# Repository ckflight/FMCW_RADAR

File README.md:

# Frequency Modulated Continuous Wave Radar Hardware Design and the Firmware

Check the new design's Python files for better processing and analysis https://github.com/ckflight/FMCW_RADAR_2v2

#### Later Update 1: 
  New version of the hardware is available in the **Radar 2** folder. For **Radar 2** design, two separated boards in **Radar MCU** and **Radar RF** folders are brought together with several necessary improvements. I recommend using the second design since it is more reliable and tested. The reason behind two separate board was to change digital part of the board without changing the RF part of it. However, one united design performs better and have a better temperature cooling control which affect the overall perfomance significantly.
  
  ##### Important Power Supply Note: I used switching regulator for 3.3 and 5V power sources to test their effect on the RF performance and oscillation of ripple voltage on OpAmp analog amplifier side. Therefore do not use switching regulator in your design. Change them to LDO type of clean supplies. Or add second LDO stage to the switching regulator unless you want an AM modulated ( 1.4 MHz switching freq. is very visible ) signal at the OpAmp side. After observing these affects i had to fine tune components which is not necessary if you use a cleaner source !!!

#### Later Update 2: 
  I have added a new Python script for plotting the radar data with Python Qt5 and Vispy plotting tool which uses GPU instead of CPU. Radar_Plot2.py is the source code. New code plots the time domain and frequency domain data together with scale and restart options. It has thread based approach between Vispy and Qt classes by using DataSource which allows us to manage more data. See first screenshot under Python Script Plots section below.

#### Radar Info:
 * Frequency Modulated Continuous Wave Radar with 26 dBm output power covering around 250 meters range with 10 dBi gain patch antenna (400 meters in theory by using a better ADC with higher sampling rate to match the noise floor of the RF receiver chain).
 
 $$ Range(radar) = {\sqrt[4]{Pt * G^2 * \lambda^2 * \sigma \over Pmin * 4\pi^3}} $$
 
  * Receiver chain has LNA, Gain Block and Mixer. The gain block drops the Noise Figure from 7 dB to 2 dB, which doubles the detection range. To determine the radar detection range, minimum detectable signal is needed. RF receiver chain has thermal noise and it determines the noise floor for Pmin. Signal to Noise (SNR) ratio of 20 dB is assumed for a good detectable signal then:
 
 $$ Pthermal(watt) = {k * T * B * F} $$
 
 $$ Pthermal(dBm) = {10\log_{10} {kT \over 1mW} + NF + 10\log_{10} BW} $$
  
 $$ Pmin(dBm) = {Pthermal(dBm) + 20dB} $$

 * Radar, has an auto gain configuration with a digital potentiometer to control intermediate frequency (IF) signal gain at the last stage of the analog amplifier before sampling with ADC.
 
 * -40 dB / Decade Range Compensation Filter is implemented. Closer objects reflect more powerful RF signal which suppresses the signal of the objects at further distance. By amplifying the weaker signals and filtering the closer ones, each frequency band is adjusted to the same amplitude.
 
 * The IF signal is available at different stages of the amplifier and filter circuit for testing with other configurations.

 * The VCO range of the radar is from 5.5 to 6.1 GHz
 
 * Directional coupler has low insertion loss of 0.25 dB and 16 dB coupling.
 
 * ADF4158 Frequency Synthesizer is available due to the nonlinear characteristics of the VCO profile for accurate distance detection. ADF4158 can generate pulses with some gap between each sweep. During this gap samples are packed and buffered over USB.
 
  * STM32F4's DAC has a triangular waveform generation option and it can be used for VCO signal generation as well. Both option are available on board. Check schematic to populate necessary resistor values to use either mode.
 
 * SMA connector has 1 mm pad size, but the 50 Ohm transmission line is 0.342 mm wide. To prevent reflection, cutout is implemented beneath the SMA pad with CST Studio simulation which is also available at my repository https://github.com/ckflight/CST_ADS_MODELS_SIMULATIONS

 * PCB has 4 layers. 50 Ohm impedance microstrip transmission line is making 0.342mm trace width by using oshpark's stack-up below. Stack-up layer information can be found here: https://docs.oshpark.com/services/four-layer/

 * Main loop runs with a Finite State Machine (FSM) to control radar, which checks the condition of the start of the sweep and the gap. ADF4158 Muxout is generating a pulse according to the sweep condition. External interrupt tracks this pulse to move between FSM states. 

 * Hardware is configured using Python script so the PC is in Host mode and controls everything. In this way, any hardware parameters can be changed without reflashing the firmware.

 * N number of samples are determined by sweep bandwidth rise time and the sampling frequency. 
   For example:

   Fs = 500.000 samples/sec and the sweep rise time is 1 millisecond (ms) for 200 MHz bandwidth. The system will pack 500 x  16 bit ADC samples and transfer 1000 x 8 bit ADC samples to Python script in 1 ms. Therefore, 1 MegaByte data is buffered to Host PC for 500 KHz sampling frequency in 1 second.
  
 * Python Script: I have uploaded an example record file along with python scripts where the peaks of the stationary objects can be seen. 

### Object Type Detection:

 * Object type detection is done with the similar code that i wrote for my project at the repository https://github.com/ckflight/RADAR_24GHZ_NEURAL_NETWORK
 
## RADAR 2 Screenshot:

## RADAR 1 RF Board Screenshot:

## RADAR 1 MCU Board Screenshot:

## Python Script Plots:

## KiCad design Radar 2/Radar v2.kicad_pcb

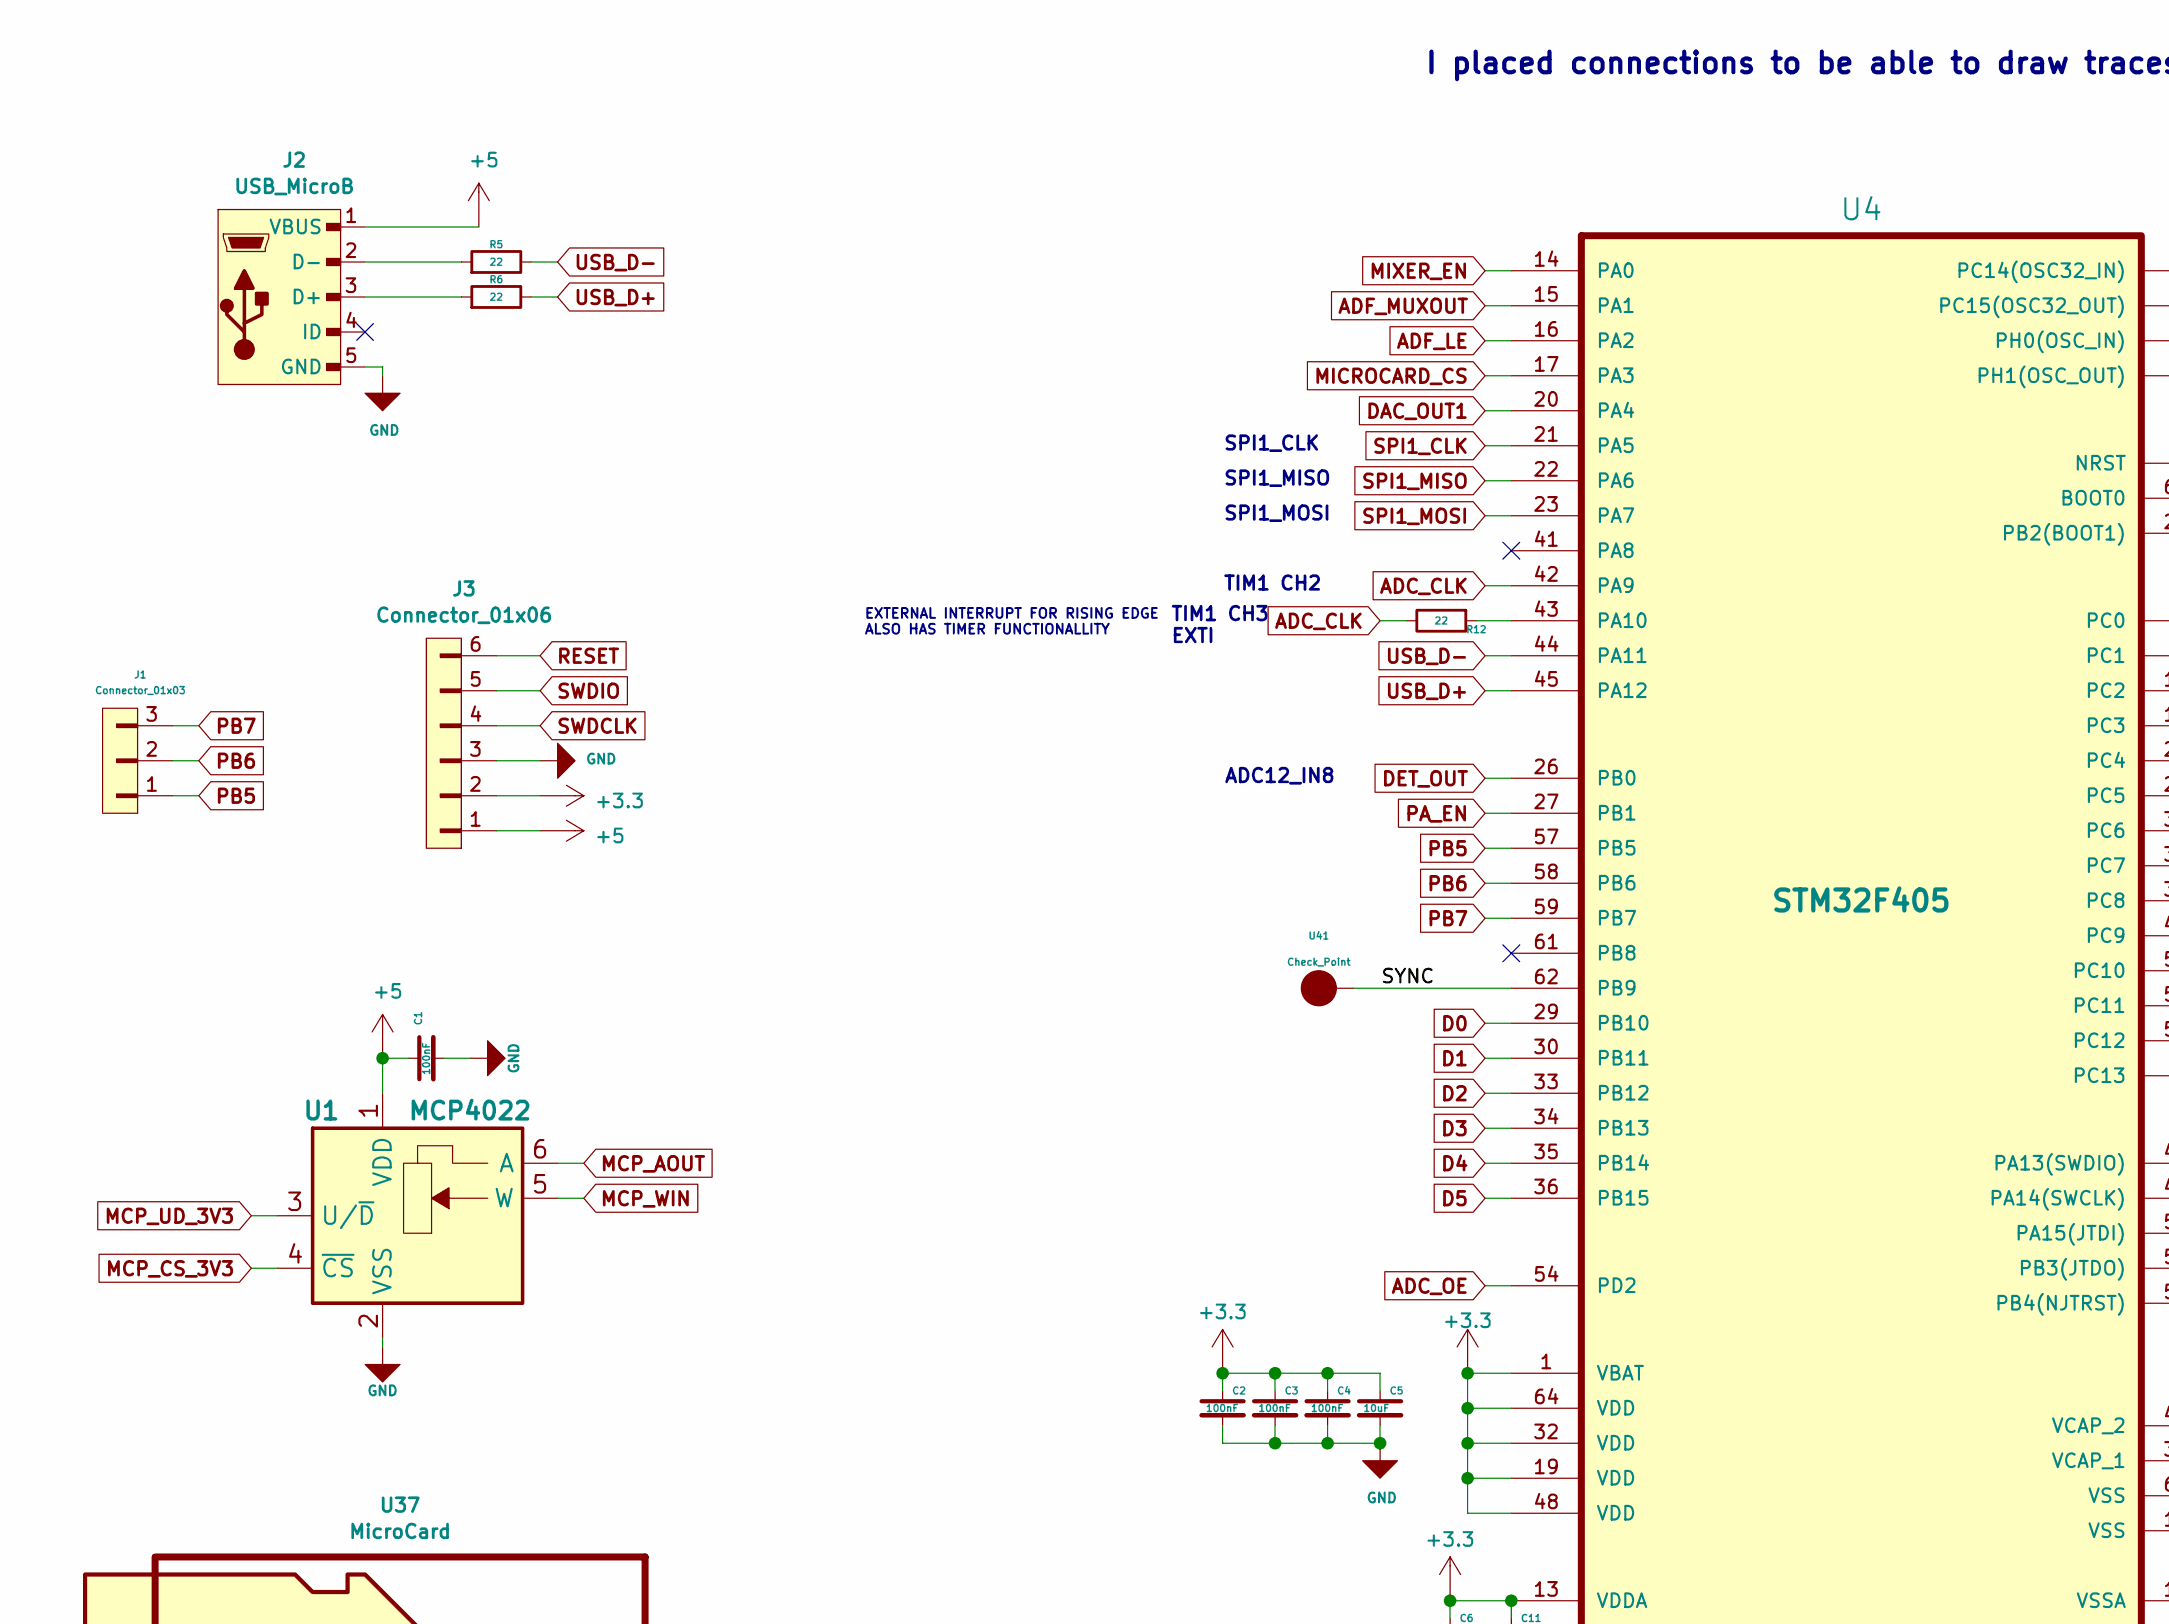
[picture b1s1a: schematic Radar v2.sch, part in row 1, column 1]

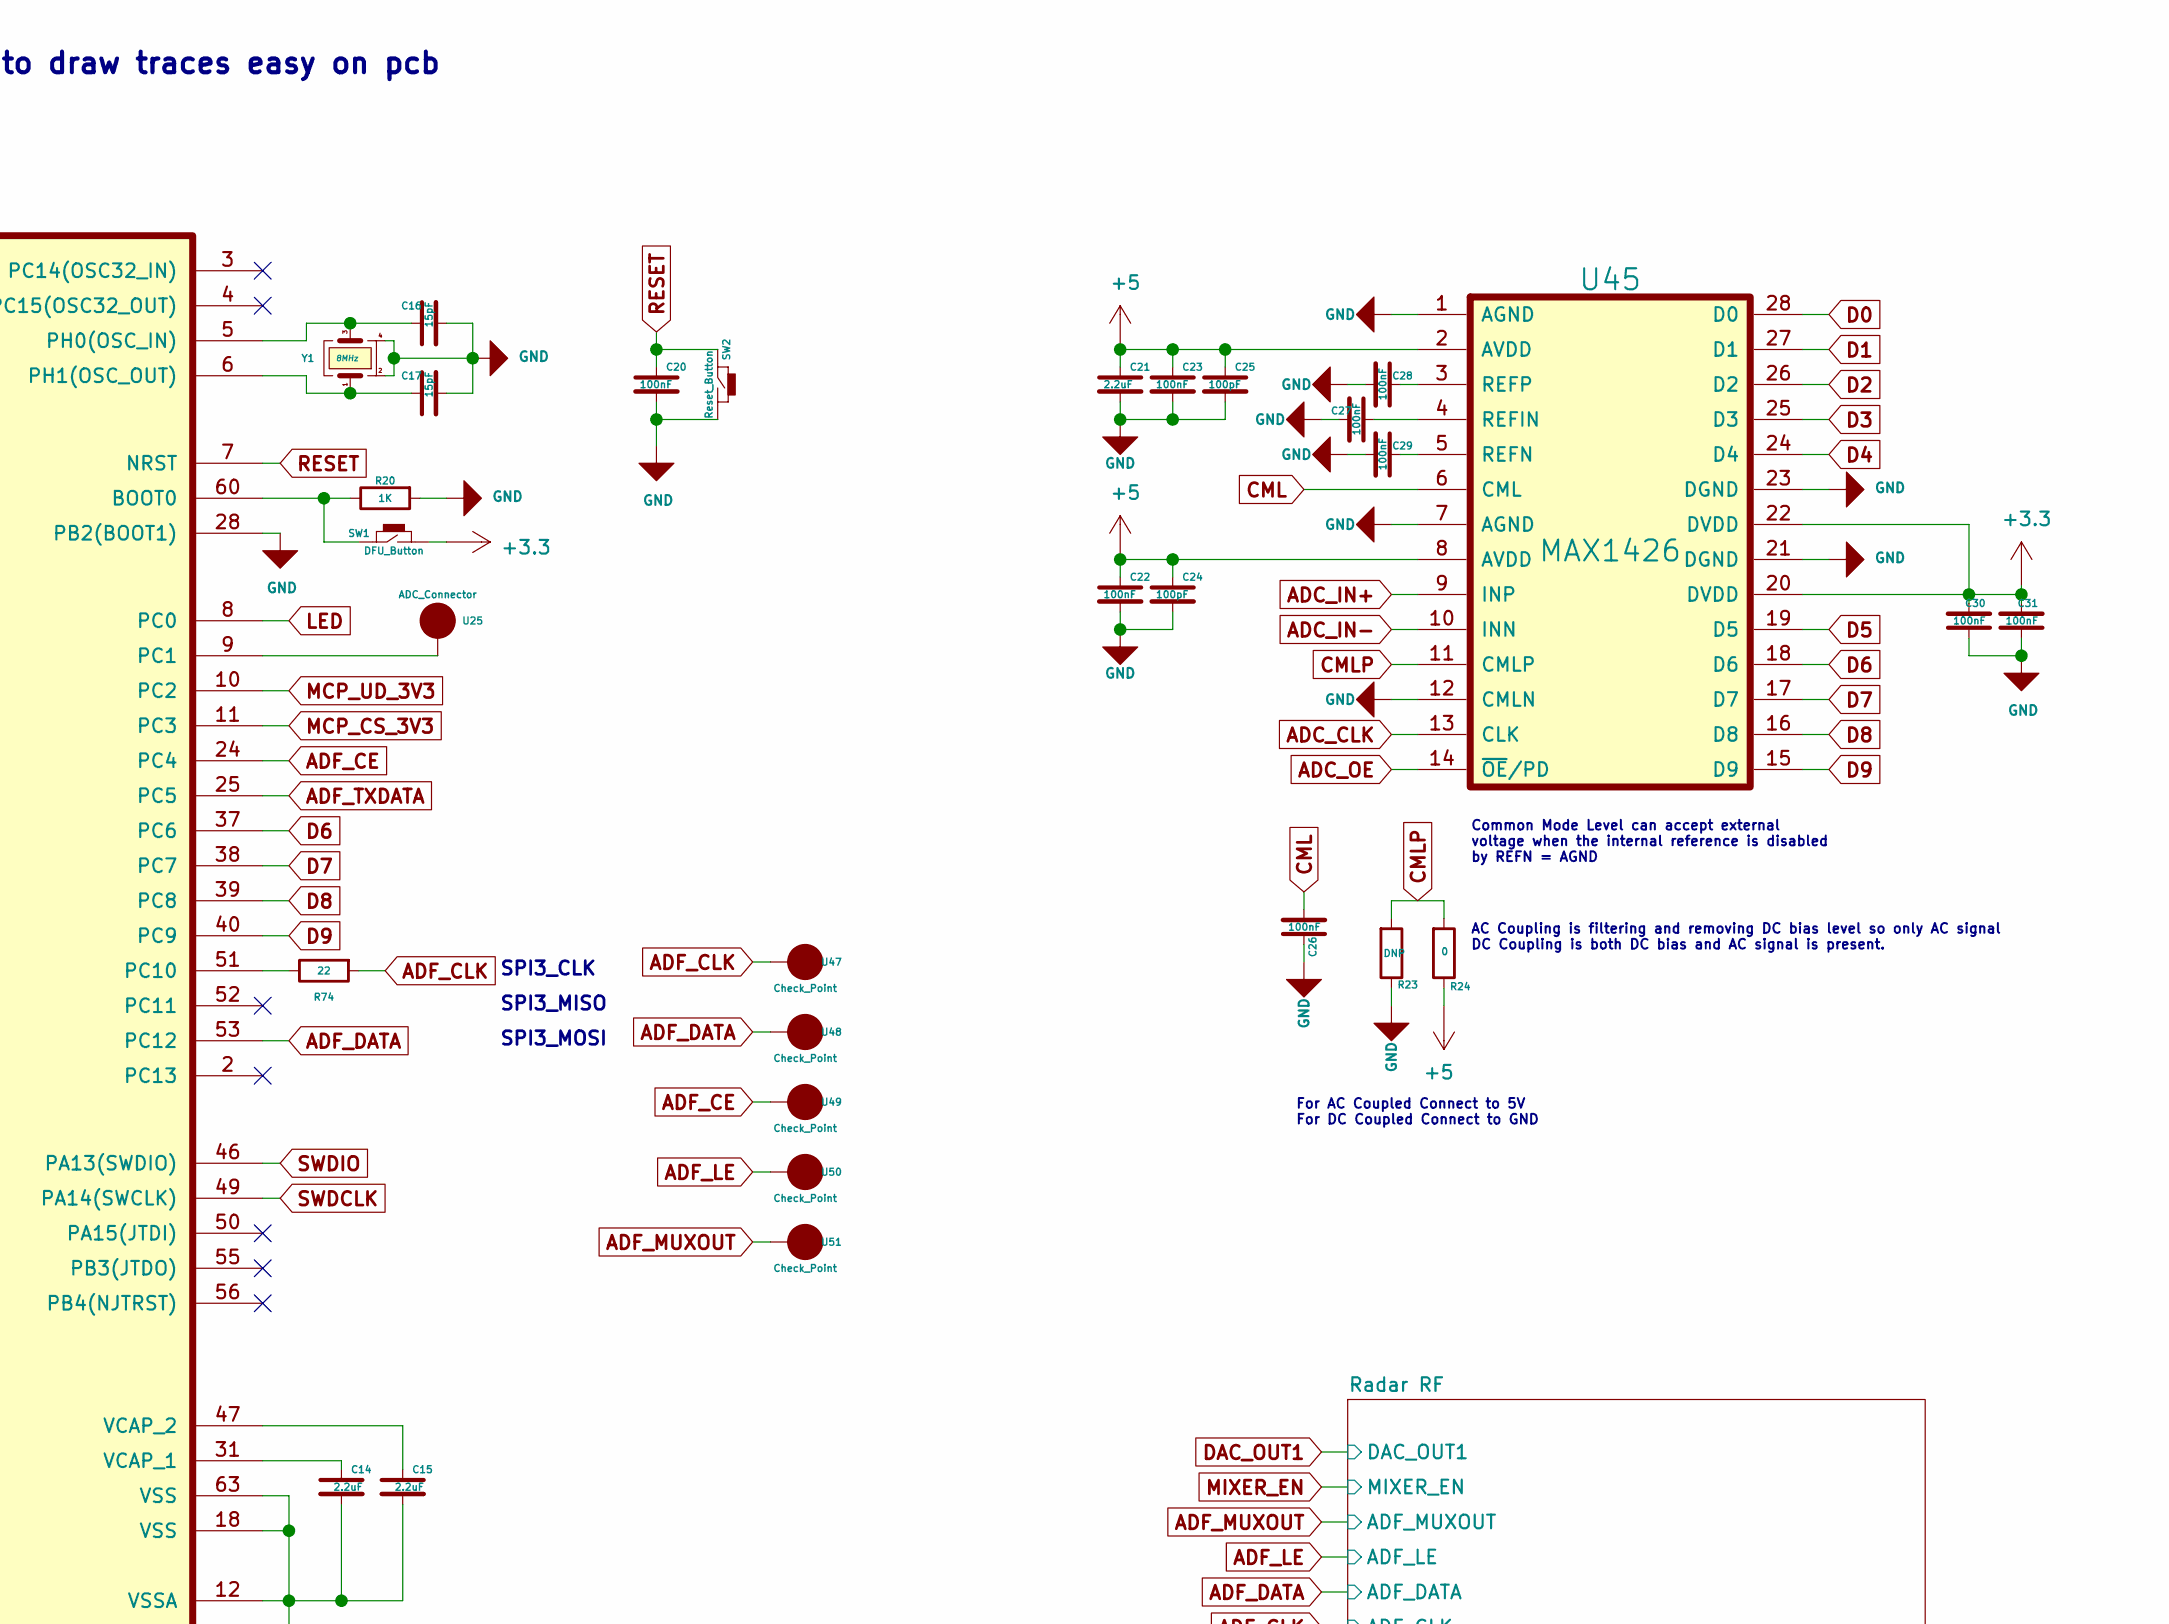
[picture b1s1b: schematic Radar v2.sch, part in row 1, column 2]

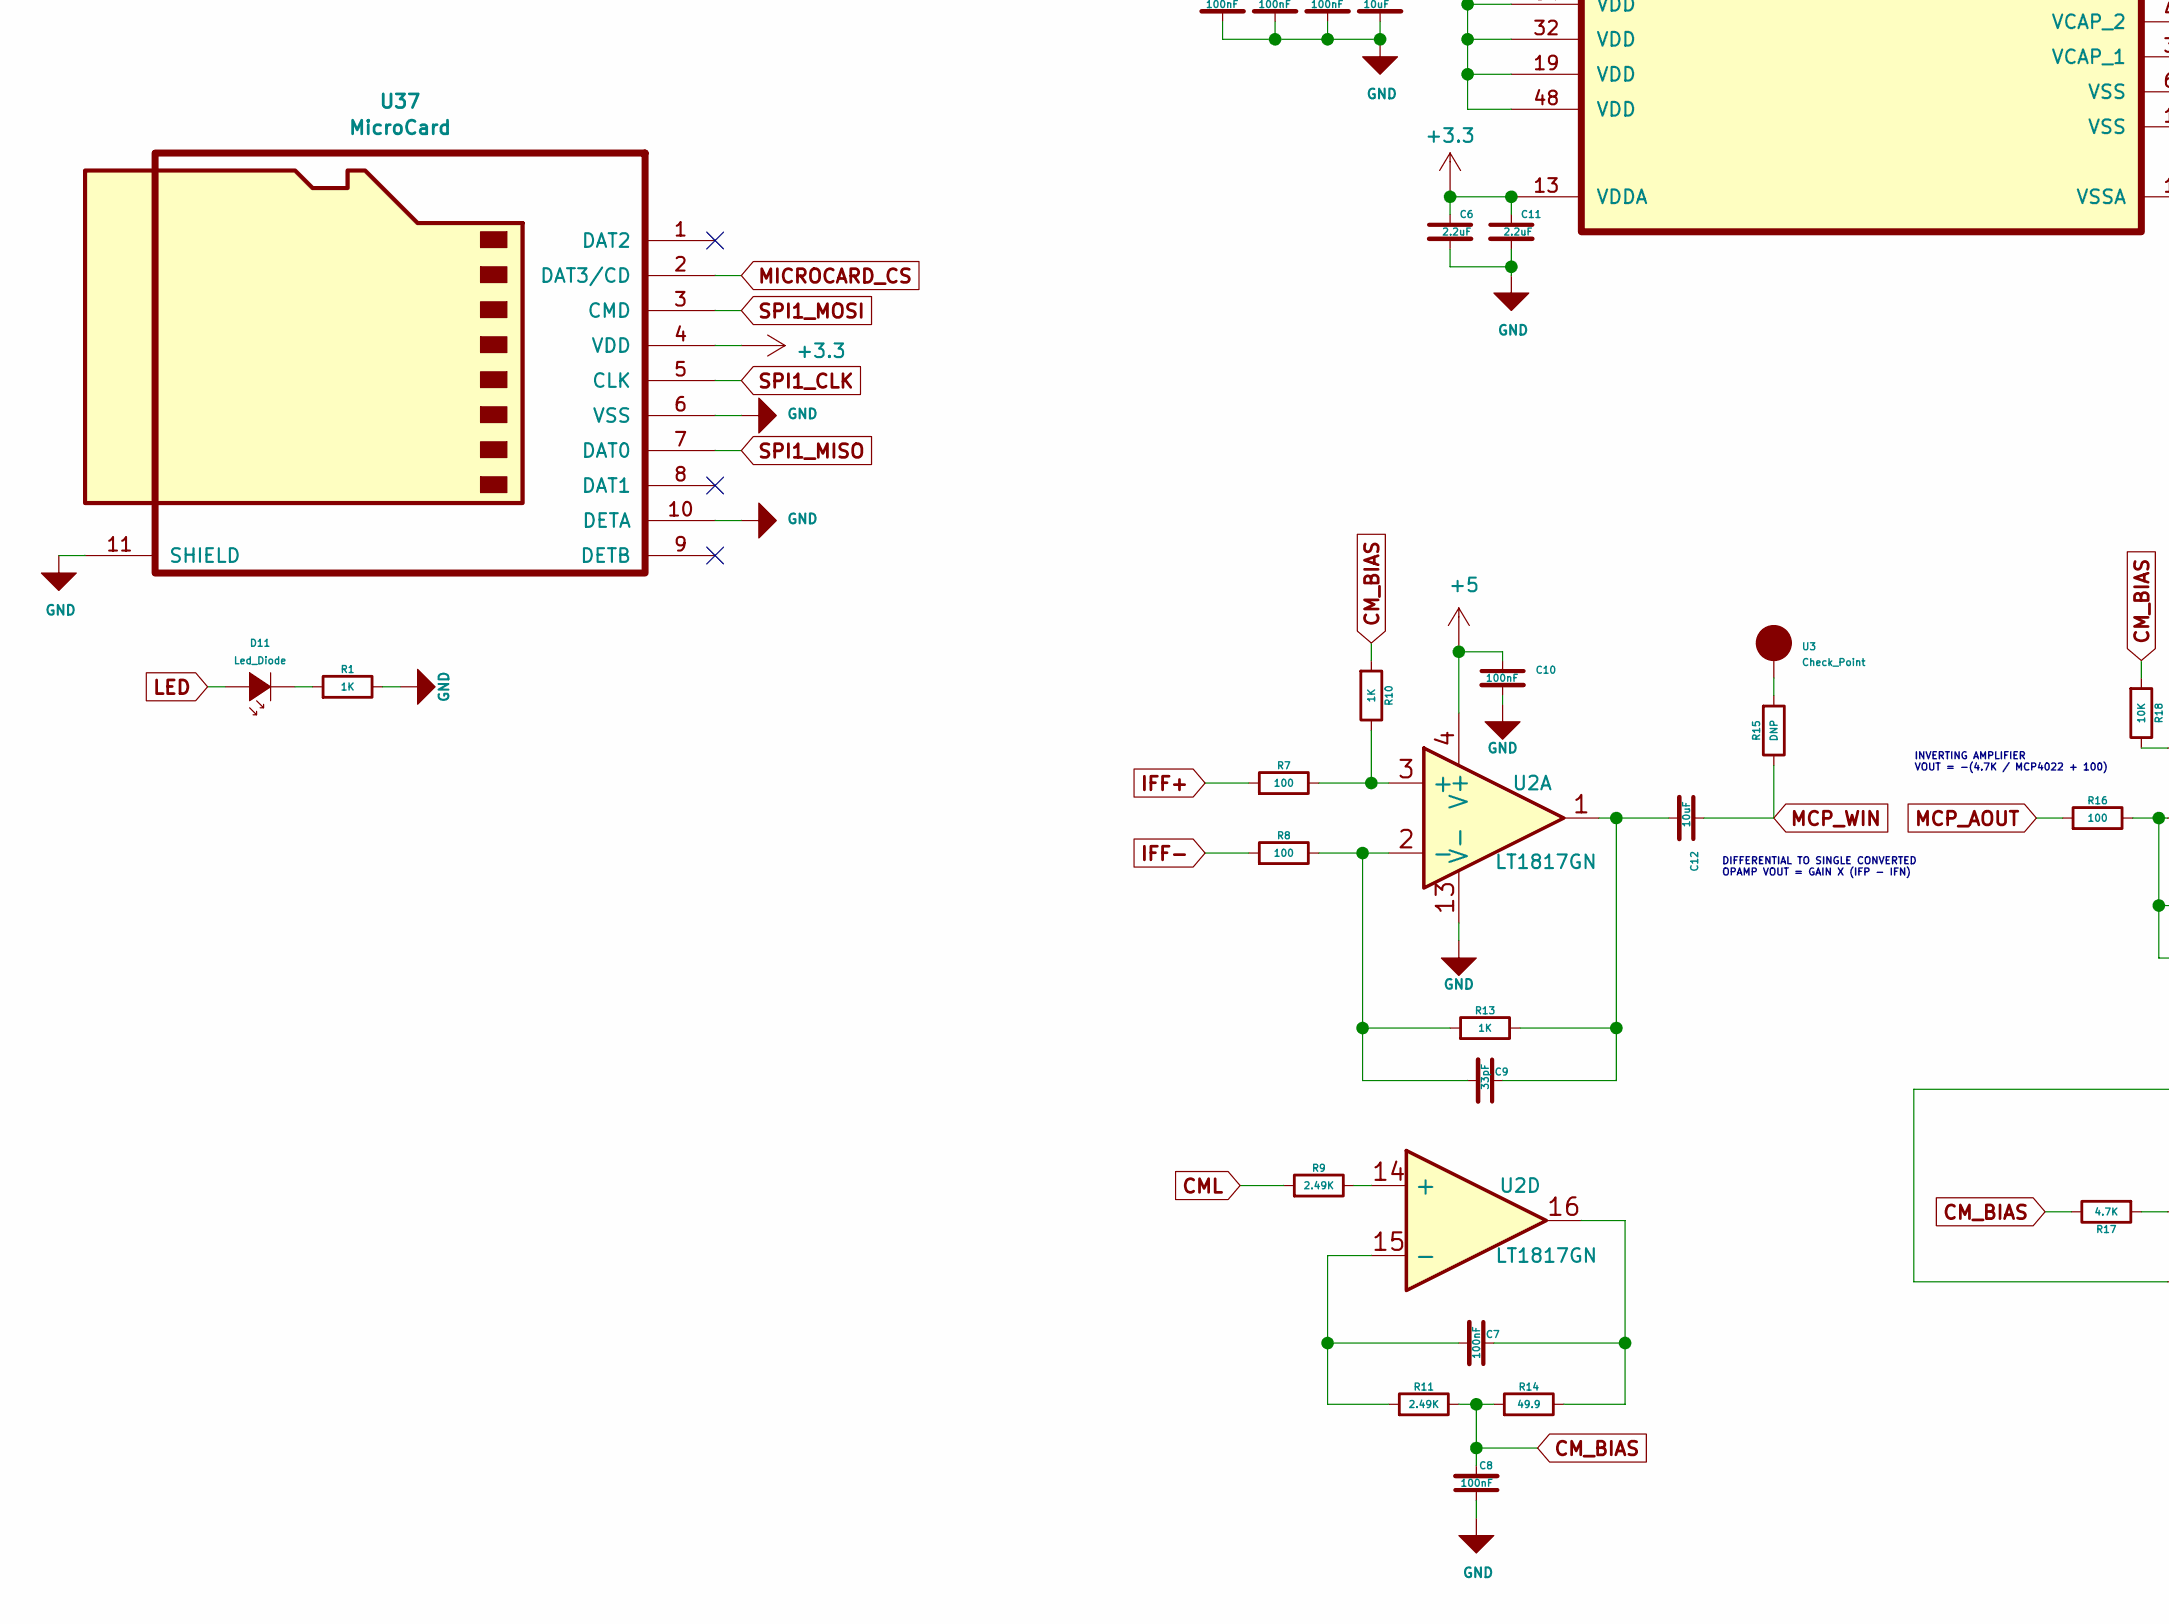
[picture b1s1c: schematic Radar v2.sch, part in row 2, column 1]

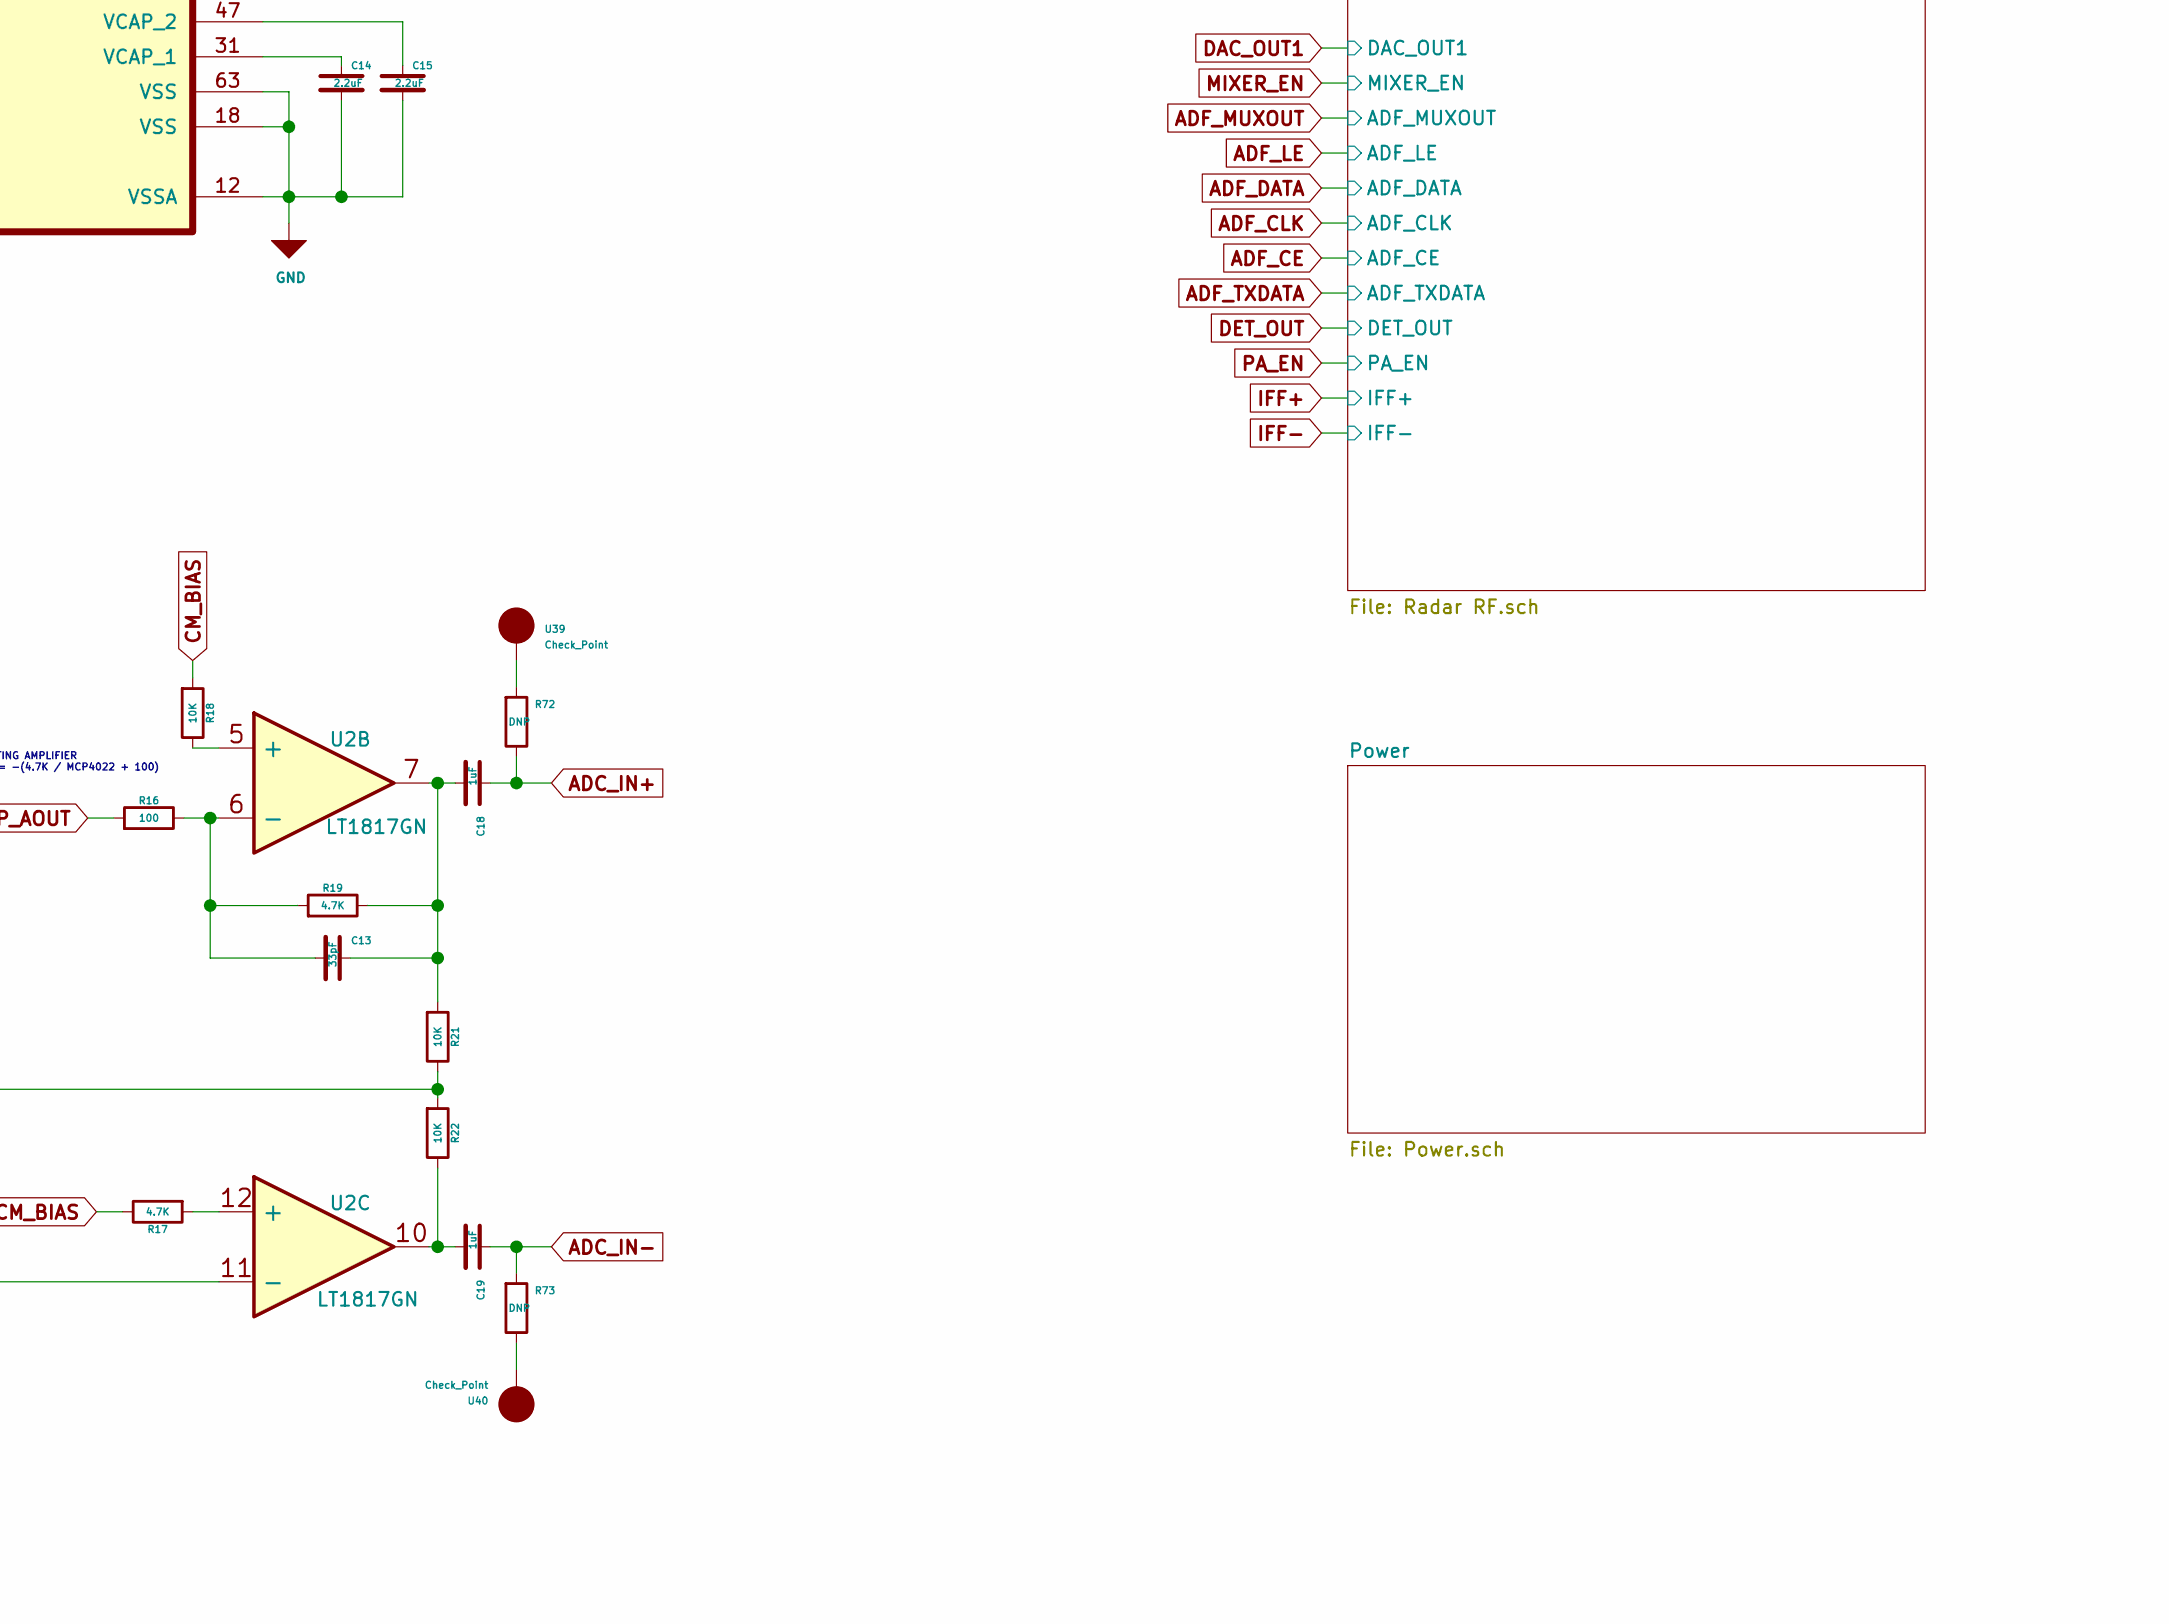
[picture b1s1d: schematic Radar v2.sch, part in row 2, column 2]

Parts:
C1, C2, C3, C4, C7, C8, C10, C20, C22, C23, C26, C27, C28, C29, C30, C31: 100nF; SMD_0402
C5, C12: 10uF; SMD_0603
C6, C11, C14, C15, C21: 2.2uF; SMD_0402
C9, C13: 33pF; SMD_0402
C16, C17: 15pF; SMD_0402
C18, C19: 1uF; SMD_0402
C24, C25: 100pF; SMD_0402
D11: Led_Diode; Diode_0603
J1: Connector_01x03; PinHeader_1x3_P2.5mm
J2: USB_MicroB; USB_MicroB_TH
J3: Connector_01x06; PinHeader_1x6_P2.5mm
R1, R10, R13, R20: 1K; SMD_0402
R5, R6, R12, R74: 22; SMD_0402
R7, R8, R16: 100; SMD_0402
R9, R11: 2.49K; SMD_0402
R14: 49.9; SMD_0402
R15, R23, R72, R73: DNP; SMD_0402
R17, R19: 4.7K; SMD_0402
R18, R21, R22: 10K; SMD_0402
R24: 0; SMD_0402
SW1: DFU_Button; Button_B3U_1000P
SW2: Reset_Button; Button_B3U_1000P
U1: MCP4022; SOT23_6
U2: LT1817GN; SSOP16_3.9x4.9mm_P0.635mm
U3, U39, U40, U41: Check_Point; SolderPad_1_1.5mm_SMD_Circle
U4: STM32F405; LQFP64_10x10mm_P0.5mm
U25: ADC_Connector; SolderPad_1_1.5mm_SMD_Circle
U37: MicroCard; MICROCARD_DM3AT_SF_PEJM5
U45: MAX1426; SSOP28_5.3x10.2mm_P0.65mm
U47, U48, U49, U50, U51: Check_Point; SolderPad_1_1.2mm_SMD_Circle
Y1: 8MHz; Crystal_3.2x2.5mm

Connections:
+3.3: C2.1, C3.1, C4.1, C5.1, C6.1, C11.1, C30.2, C31.2, J3.2, SW1.2, U4.1 (VBAT), U4.13 (VDDA), U4.19 (VDD), U4.32 (VDD), U4.48 (VDD), U4.64 (VDD), U37.4 (VDD), U45.20 (DVDD), U45.22 (DVDD); also elsewhere on the board
+5: C1.1, C10.1, C21.1, C22.1, C23.1, C24.1, C25.1, J2.1 (VBUS), J3.1, R24.2, U1.1 (VDD), U2.4 (V+), U45.2 (AVDD), U45.8 (AVDD); also elsewhere on the board
/SYNC: U4.62 (PB9), U41.1
ADC_CLK: R12.2, U4.42 (PA9), U45.13 (CLK)
ADC_IN+: C18.1, R72.2, U45.9 (INP)
ADC_IN-: C19.1, R73.1, U45.10 (INN)
ADC_OE: U4.54 (PD2), U45.14 (~OE~/PD)
ADF_CE: U4.24 (PC4), U49.1; also elsewhere on the board
ADF_CLK: R74.1, U47.1; also elsewhere on the board
ADF_DATA: U4.53 (PC12), U48.1; also elsewhere on the board
ADF_LE: U4.16 (PA2), U50.1; also elsewhere on the board
ADF_MUXOUT: U4.15 (PA1), U51.1; also elsewhere on the board
ADF_TXDATA: U4.25 (PC5); also elsewhere on the board
CML: C26.2, R9.1, U45.6 (CML)
CMLP: R23.1, R24.1, U45.11 (CMLP)
CM_BIAS: C8.2, R10.1, R11.2, R14.1, R17.2, R18.1
D0: U4.29 (PB10), U45.28 (D0)
D1: U4.30 (PB11), U45.27 (D1)
D2: U4.33 (PB12), U45.26 (D2)
D3: U4.34 (PB13), U45.25 (D3)
D4: U4.35 (PB14), U45.24 (D4)
D5: U4.36 (PB15), U45.19 (D5)
D6: U4.37 (PC6), U45.18 (D6)
D7: U4.38 (PC7), U45.17 (D7)
D8: U4.39 (PC8), U45.16 (D8)
D9: U4.40 (PC9), U45.15 (D9)
DAC_OUT1: U4.20 (PA4); also elsewhere on the board
DET_OUT: U4.26 (PB0); also elsewhere on the board
GND: C1.2, C2.2, C3.2, C4.2, C5.2, C6.2, C8.1, C10.2, C11.2, C14.2, C15.2, C16.2, C17.2, C20.2, C21.2, C22.2, C23.2, C24.2, C25.2, C26.1, C27.2, C28.2, C29.2, C30.1, C31.1, J2.5 (GND), J3.3, R1.2, R20.1, R23.2, SW2.2, U1.2 (VSS), U2.13 (V-), U4.12 (VSSA), U4.18 (VSS), U4.28 (PB2(BOOT1)), U4.63 (VSS), U37.6 (VSS), U37.10 (DETA), U37.11 (SHIELD), U45.1 (AGND), U45.7 (AGND), U45.12 (CMLN), U45.21 (DGND), U45.23 (DGND), Y1.2, Y1.4; also elsewhere on the board
IFF+: R7.1; also elsewhere on the board
IFF-: R8.1; also elsewhere on the board
LED: D11.2 (A), U4.8 (PC0)
MCP_AOUT: R16.1, U1.6 (A)
MCP_CS_3V3: U1.4 (~CS), U4.11 (PC3)
MCP_UD_3V3: U1.3 (U/~D), U4.10 (PC2)
MCP_WIN: C12.1, R15.2, U1.5 (W)
MICROCARD_CS: U4.17 (PA3), U37.2 (DAT3/CD)
MIXER_EN: U4.14 (PA0); also elsewhere on the board
unnamed: C7.1, R14.2, U2.16
unnamed: C7.2, R11.1, U2.15 (-)
unnamed: C9.2, R8.2, R13.1, U2.2 (-)
unnamed: C9.1, C12.2, R13.2, U2.1
unnamed: C13.1, C18.2, R19.2, R21.1, U2.7
unnamed: C13.2, R16.2, R19.1, U2.6 (-)
unnamed: C14.1, U4.31 (VCAP_1)
unnamed: C15.1, U4.47 (VCAP_2)
unnamed: C16.1, U4.5 (PH0(OSC_IN)), Y1.3
unnamed: C17.1, U4.6 (PH1(OSC_OUT)), Y1.1
unnamed: C19.2, R22.2, U2.10
unnamed: C27.1, U45.4 (REFIN)
unnamed: C28.1, U45.3 (REFP)
unnamed: C29.1, U45.5 (REFN)
unnamed: D11.1 (K), R1.1
unnamed: J2.2 (D-), R5.1
unnamed: J2.3 (D+), R6.1
unnamed: R9.2, U2.14 (+)
unnamed: R7.2, R10.2, U2.3 (+)
unnamed: R12.1, U4.43 (PA10)
unnamed: R15.1, U3.1
unnamed: R17.1, U2.12 (+)
unnamed: R18.2, U2.5 (+)
unnamed: R20.2, SW1.1, U4.60 (BOOT0)
unnamed: R21.2, R22.1, U2.11 (-)
unnamed: R72.1, U39.1
unnamed: R73.2, U40.1
unnamed: R74.2, U4.51 (PC10)
unnamed: U4.9 (PC1), U25.1
PA_EN: U4.27 (PB1); also elsewhere on the board
PB5: J1.1, U4.57 (PB5)
PB6: J1.2, U4.58 (PB6)
PB7: J1.3, U4.59 (PB7)
RESET: C20.1, J3.6, SW2.1, U4.7 (NRST)
SPI1_CLK: U4.21 (PA5), U37.5 (CLK)
SPI1_MISO: U4.22 (PA6), U37.7 (DAT0)
SPI1_MOSI: U4.23 (PA7), U37.3 (CMD)
SWDCLK: J3.4, U4.49 (PA14(SWCLK))
SWDIO: J3.5, U4.46 (PA13(SWDIO))
USB_D+: R6.2, U4.45 (PA12)
USB_D-: R5.2, U4.44 (PA11)

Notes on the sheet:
SPI1_MOSI
SPI1_CLK
ADC12_IN8
For AC Coupled Connect to 5V For DC Coupled Connect to GND
Common Mode Level can accept external voltage when the internal reference is disabled by REFN = AGND
AC Coupling is filtering and removing DC bias level so only AC signal DC Coupling is both DC bias and AC signal is present.
DIFFERENTIAL TO SINGLE CONVERTED OPAMP VOUT = GAIN X (IFP - IFN)
INVERTING AMPLIFIER VOUT = -(4.7K / MCP4022 + 100)
TIM1 CH2
EXTERNAL INTERRUPT FOR RISING EDGE ALSO HAS TIMER FUNCTIONALLITY
SPI1_MISO
TIM1 CH3 EXTI
I placed connections to be able to draw traces easy on pcb
SPI3_CLK
SPI3_MISO
SPI3_MOSI
